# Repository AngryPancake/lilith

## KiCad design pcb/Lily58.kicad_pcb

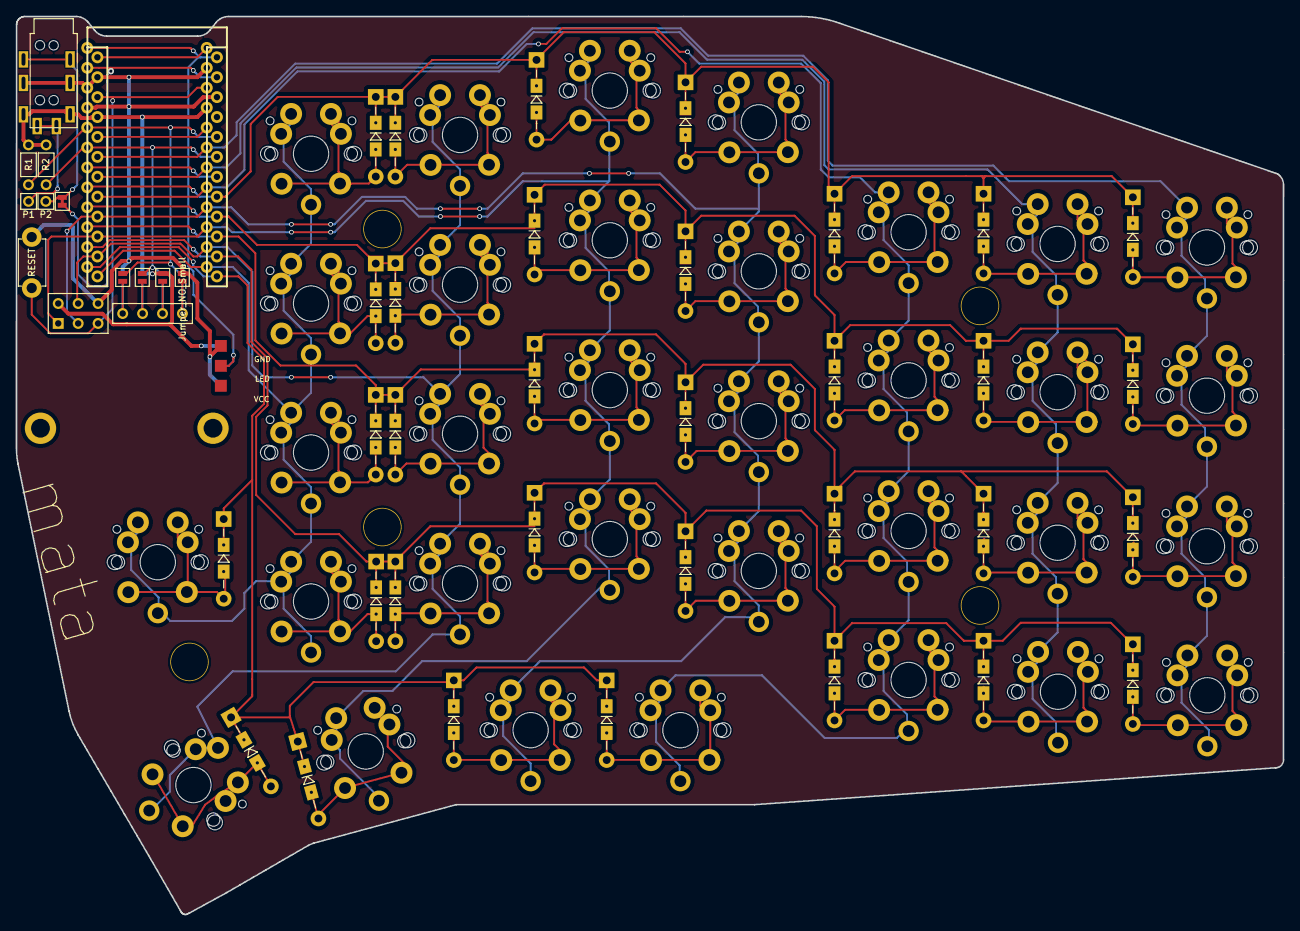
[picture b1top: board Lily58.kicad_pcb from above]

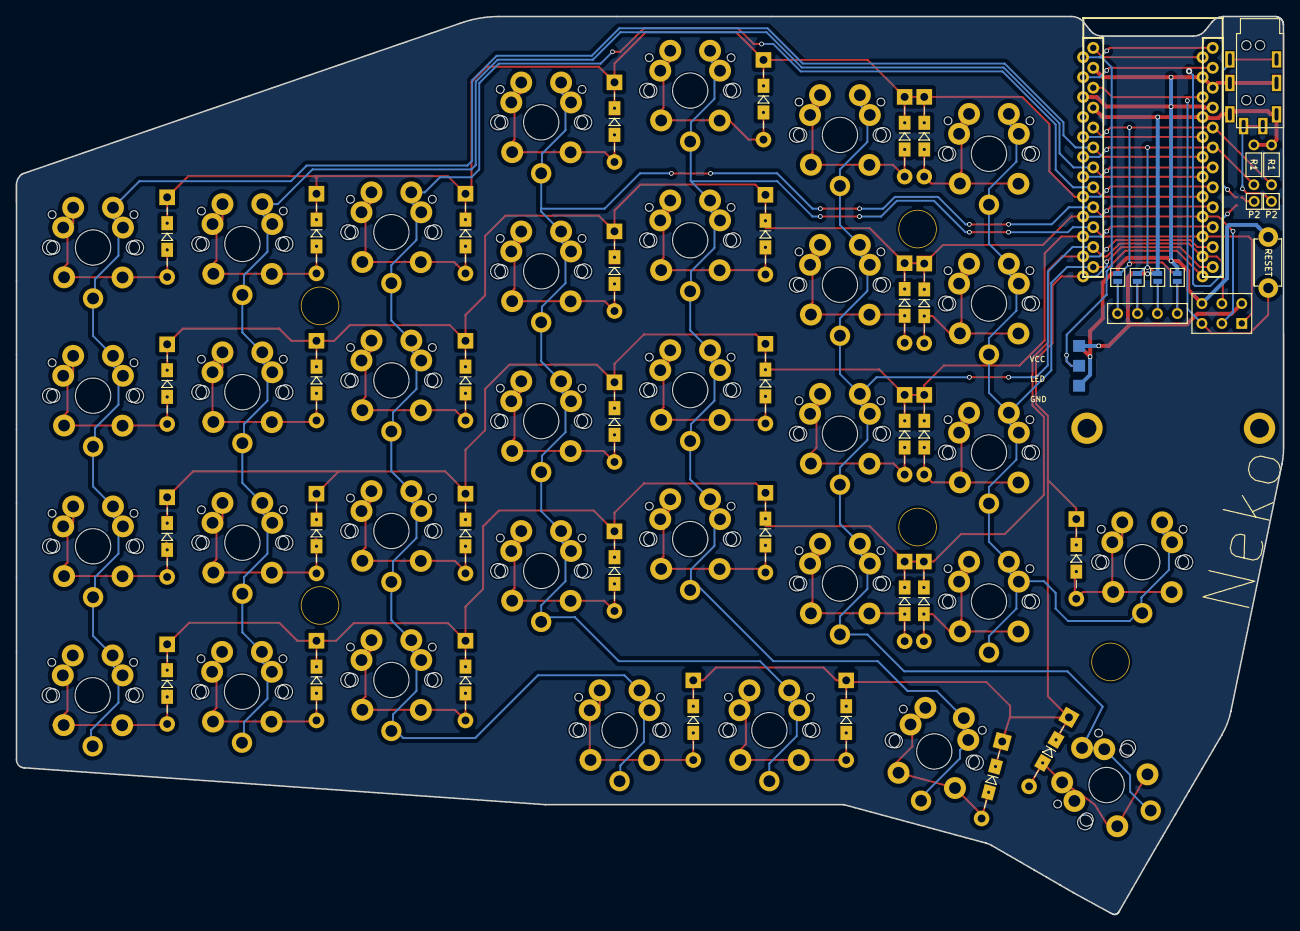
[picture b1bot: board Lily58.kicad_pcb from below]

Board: 2 copper layers, 161.6 x 114.5 mm, 92 parts (4 on the bottom side), 58 nets.

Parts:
D1, D2, D3, D4, D5, D6, D6#2, D7, D8, D9, D10, D11, D12, D12#2, D13, D14, D15, D16, D17, D18, D18#2, D19, D20, D21, D22, D23, D24, D24#2, D25, D26, D27, D28, D29: D; Diode_TH_SOD123
J1: LED; StripLED
J2: 4PIN; MJ-4PP-9
JP1, JP2, JP3, JP4, JP5, JP6, JP7, JP8: Jumper_NO_Small; Jumper
P1, P2: i2c_pin; 1pin_conn
P3: ICSP
P4: OLED; MY_SIL-4
R1, R2: R; RESISTOR_mini
RSW1: SW_RST; TACT_SWITCH_TVBP06
SW1, SW2, SW3, SW4, SW5, SW6, SW6#2, SW7, SW8, SW9, SW10, SW11, SW12, SW12#2, SW13, SW14, SW15, SW16, SW17, SW18, SW18#2, SW19, SW20, SW21, SW22, SW23, SW24, SW24#2, SW25, SW27, SW28, SW29: SW_PUSH; MX_PG1350-Under_FLIP_HOLES_18mm
SW26: SW_PUSH; MX_PG1350-Under_FLIP_HOLES_27mm
TH1, TH2: HOLE; M2_HOLE_PCB
TH3, TH4, TH5, TH6, TH7: HOLE; HOLE_M2_TH
U1: ProMicro; ProMicro_rev2
W1: jumper; jumper_data

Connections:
DATA: U1.2 (RX(PD2)), W1.1
GND: J1.3, J2.2, JP1.2, JP8.2, P3.6, RSW1.1, U1.3 (GND), U1.4 (GND), U1.23 (GND)
LED: J1.2, U1.1 (TX(PD3))
unnamed: D1.2 (A), SW1.2
unnamed: D2.2 (A), SW2.2
unnamed: D3.2 (A), SW3.2
unnamed: D4.2 (A), SW4.2
unnamed: D5.2 (A), SW5.2
unnamed: D6.2 (A), SW6.2
unnamed: D6#2.2 (A), SW6#2.2
unnamed: D7.2 (A), SW7.2
unnamed: D8.2 (A), SW8.2
unnamed: D9.2 (A), SW9.2
unnamed: D10.2 (A), SW10.2
unnamed: D11.2 (A), SW11.2
unnamed: D12.2 (A), SW12.2
unnamed: D12#2.2 (A), SW12#2.2
unnamed: D13.2 (A), SW13.2
unnamed: D14.2 (A), SW14.2
unnamed: D15.2 (A), SW15.2
unnamed: D16.2 (A), SW16.2
unnamed: D17.2 (A), SW17.2
unnamed: D18.2 (A), SW18.2
unnamed: D18#2.2 (A), SW18#2.2
unnamed: D19.2 (A), SW19.2
unnamed: D20.2 (A), SW20.2
unnamed: D21.2 (A), SW21.2
unnamed: D25.2 (A), SW25.2
unnamed: D23.2 (A), SW23.2
unnamed: D24.2 (A), SW24.2
unnamed: D24#2.2 (A), SW24#2.2
unnamed: D26.2 (A), SW26.2
unnamed: D27.2 (A), SW27.2
unnamed: D28.2 (A), SW28.2
unnamed: D29.2 (A), SW29.2
unnamed: D22.2 (A), SW22.2
unnamed: J2.4, P1.1
unnamed: J2.3, P2.1, W1.2
unnamed: JP8.1, P4.1
unnamed: JP7.1, P4.2
unnamed: JP6.1, P4.3
unnamed: JP5.1, P4.4
RESET: P3.5, RSW1.2, U1.22 (RST)
SCL: JP3.2, JP6.2, R2.2, U1.6 (SCL(PD0))
SDA: JP4.2, JP5.2, R1.2, U1.5 (SDA(PD1))
VCC: J1.1, J2.1, JP2.2, JP7.2, P3.2, R1.1, R2.1, U1.21 (VCC)
col0: SW6#2.1, SW12#2.1, SW18#2.1, SW24#2.1, U1.19 (A2(PF5))
col1: SW6.1, SW12.1, SW18.1, SW24.1, U1.18 (A1(PF6))
col2: SW5.1, SW11.1, SW17.1, SW23.1, SW29.1, U1.17 (A0(PF7))
col3: P3.3, SW4.1, SW10.1, SW16.1, SW22.1, SW28.1, U1.16 (D15(PB1))
col4: P3.1, SW3.1, SW9.1, SW15.1, SW21.1, SW27.1, U1.15 (D14(PB3))
col5: P3.4, SW2.1, SW8.1, SW14.1, SW20.1, SW26.1, U1.14 (D16(PB2))
col6: SW1.1, SW7.1, SW13.1, SW19.1, SW25.1, U1.13 (D10(PB6))
row0: D1.1 (K), D2.1 (K), D3.1 (K), D4.1 (K), D5.1 (K), D6.1 (K), D6#2.1 (K), U1.8 (D5(PC6))
row1: D7.1 (K), D8.1 (K), D9.1 (K), D10.1 (K), D11.1 (K), D12.1 (K), D12#2.1 (K), U1.9 (D6(PD7))
row2: D13.1 (K), D14.1 (K), D15.1 (K), D16.1 (K), D17.1 (K), D18.1 (K), D18#2.1 (K), U1.10 (D7(PE6))
row3: D19.1 (K), D20.1 (K), D21.1 (K), D22.1 (K), D23.1 (K), D24.1 (K), D24#2.1 (K), U1.11 (D8(PB4))
row4: D25.1 (K), D26.1 (K), D27.1 (K), D28.1 (K), D29.1 (K), U1.12 (D9(PB5))
